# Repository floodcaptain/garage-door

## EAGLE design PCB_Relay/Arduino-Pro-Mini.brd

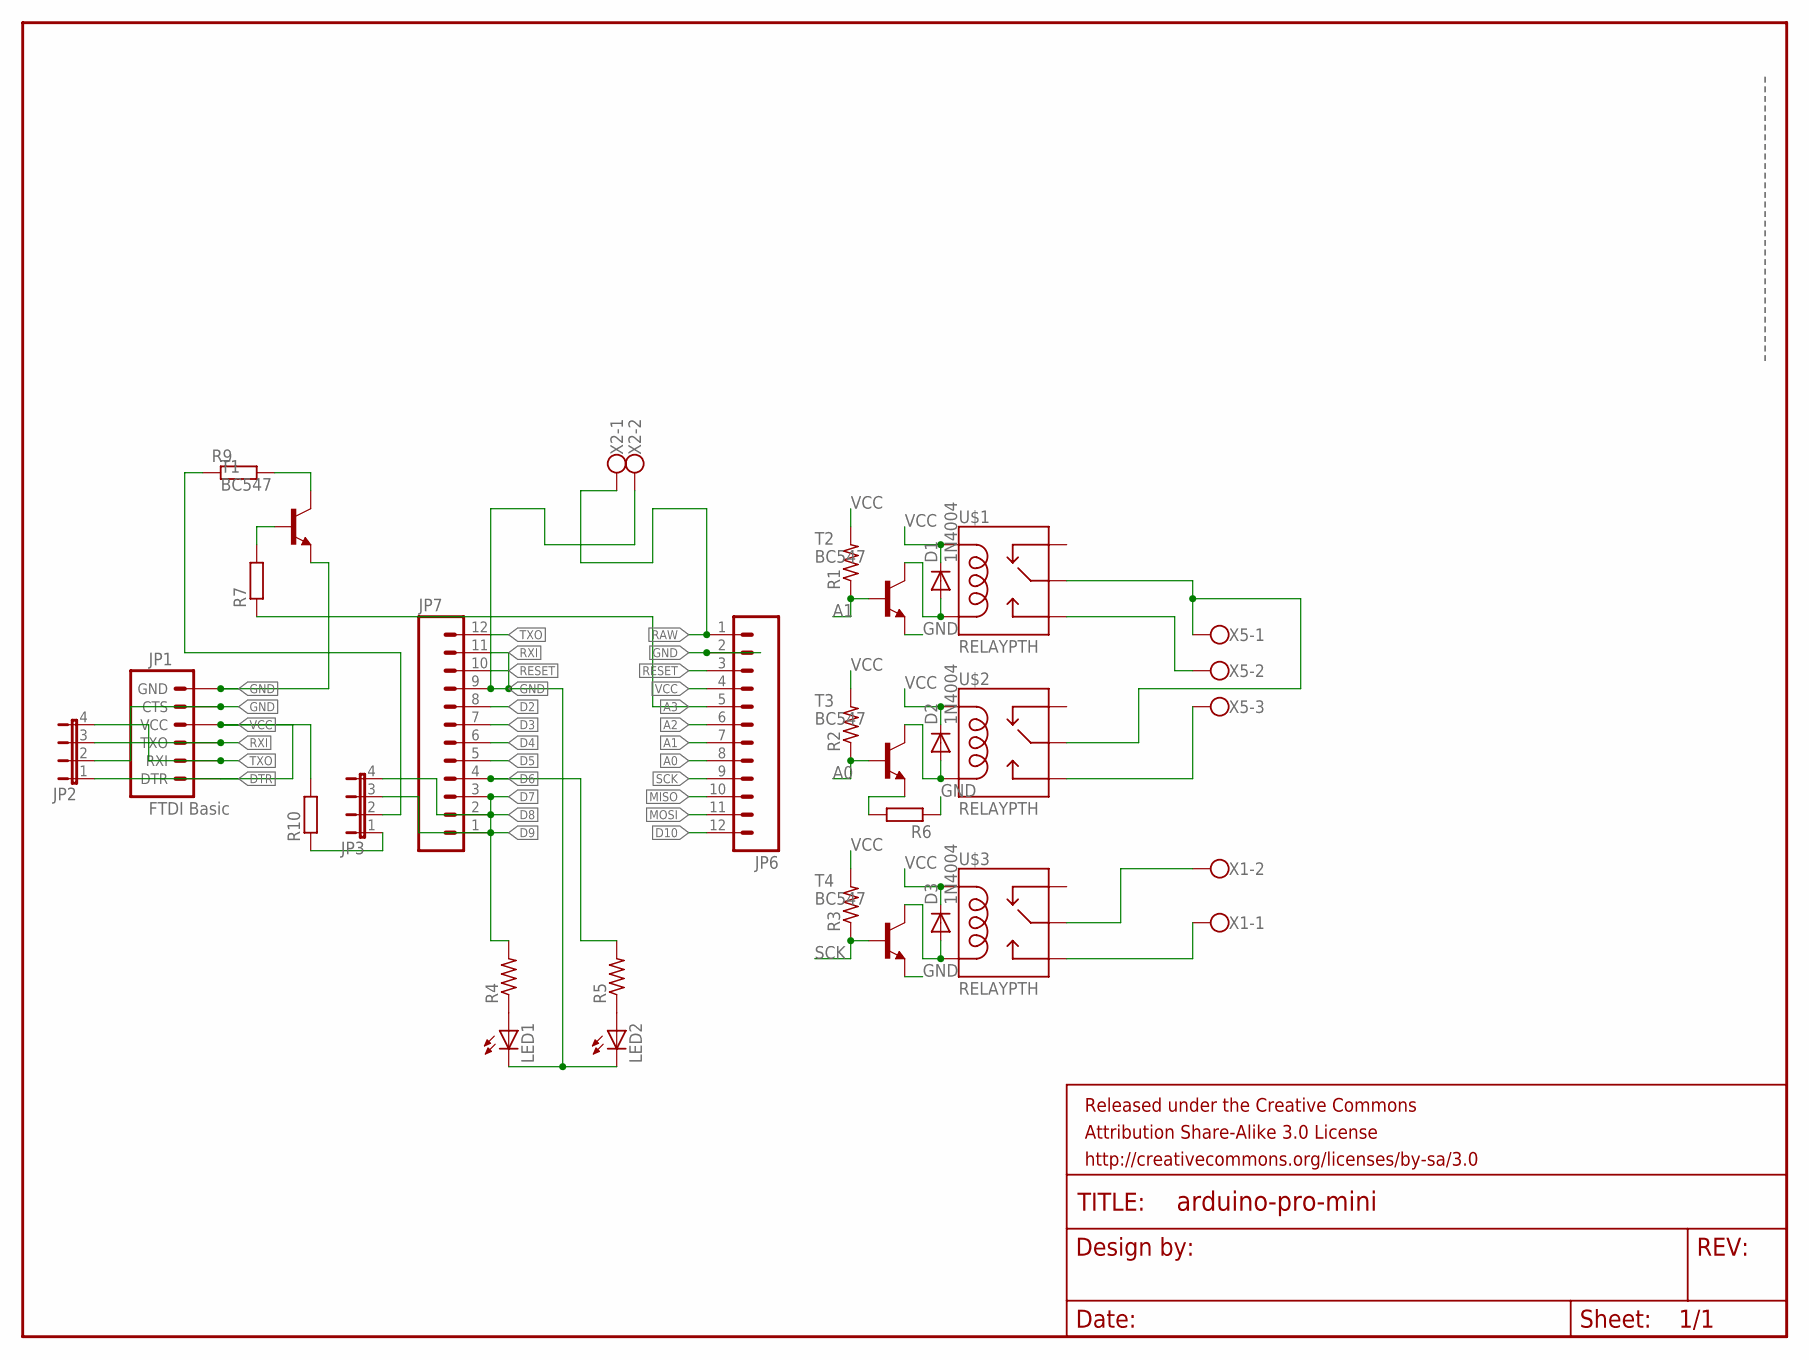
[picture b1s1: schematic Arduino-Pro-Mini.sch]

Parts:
D1, D2, D3: 1N4004; DO41-10
FRAME1: FRAME-LETTER; CREATIVE_COMMONS
JP1: FTDI Basic; 1X06
JP2, JP3: JP4E; JP4
JP6, JP7: M12PTH; 1X12
LED1, LED2: LED3MM
R1, R2, R3: R-US_0204/5; 0204/5
R4, R5: FLIPFLOP-RES; 0805-THM
R6, R10: RR1206; R1206
R7: R0204/7; 0204/7
R9: RR0603; R0603
T1, T2, T3, T4: BC547; TO92
U$1, U$2, U$3: RELAYPTH; SRD-05VDC-SL-C
X1, X2: W237-102
X5: W237-103

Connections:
A0: JP6.8, R2.1, T3.2 (B)
A1: JP6.7, R1.1, T2.2 (B)
A2: JP6.6
A3: JP6.5, R7.1
D2: JP7.8
D3: JP7.7
D4: JP7.6
D5: JP7.5
D6: JP7.4, R5.2
D7: JP7.3, R4.2
D8: JP3.4, JP7.2
D9: JP3.3, JP7.1
D10: JP6.12
DTR: JP1.1 (DTR)
GND: JP1.5 (CTS), JP1.6 (GND), JP2.2, JP6.2, JP7.9, LED1.K (C), LED2.K (C), R6.1, R6.2, T1.1 (E), T2.1 (E), T3.1 (E), T4.1 (E), X2.2
MISO: JP6.10
MOSI: JP6.11
unnamed: U$1.SWCOMMON, U$2.SWCOMMON, X5.1
unnamed: U$1.SWOPEN, X5.2
unnamed: U$2.SWOPEN, X5.3
unnamed: D3.A, T4.3 (C), U$3.COIL0
unnamed: D2.A, T3.3 (C), U$2.COIL0
unnamed: D1.A, T2.3 (C), U$1.COIL0
unnamed: U$3.SWCOMMON, X1.2
unnamed: U$3.SWOPEN, X1.1
unnamed: LED1.A, R4.1
unnamed: LED2.A, R5.1
unnamed: JP3.2, R9.1
unnamed: R7.2, T1.2 (B)
unnamed: JP3.1, R10.1
unnamed: R9.2, T1.3 (C)
RAW: JP6.1, X2.1
RESET: JP6.3, JP7.10
RXI: JP1.3 (TXO), JP2.3, JP7.11
SCK: JP6.9, R3.1, T4.2 (B)
TXO: JP1.2 (RXI), JP2.4, JP7.12
VCC: D1.C, D2.C, D3.C, JP1.4 (VCC), JP2.1, JP6.4, R1.2, R2.2, R3.2, R10.2, U$1.COIL1, U$2.COIL1, U$3.COIL1

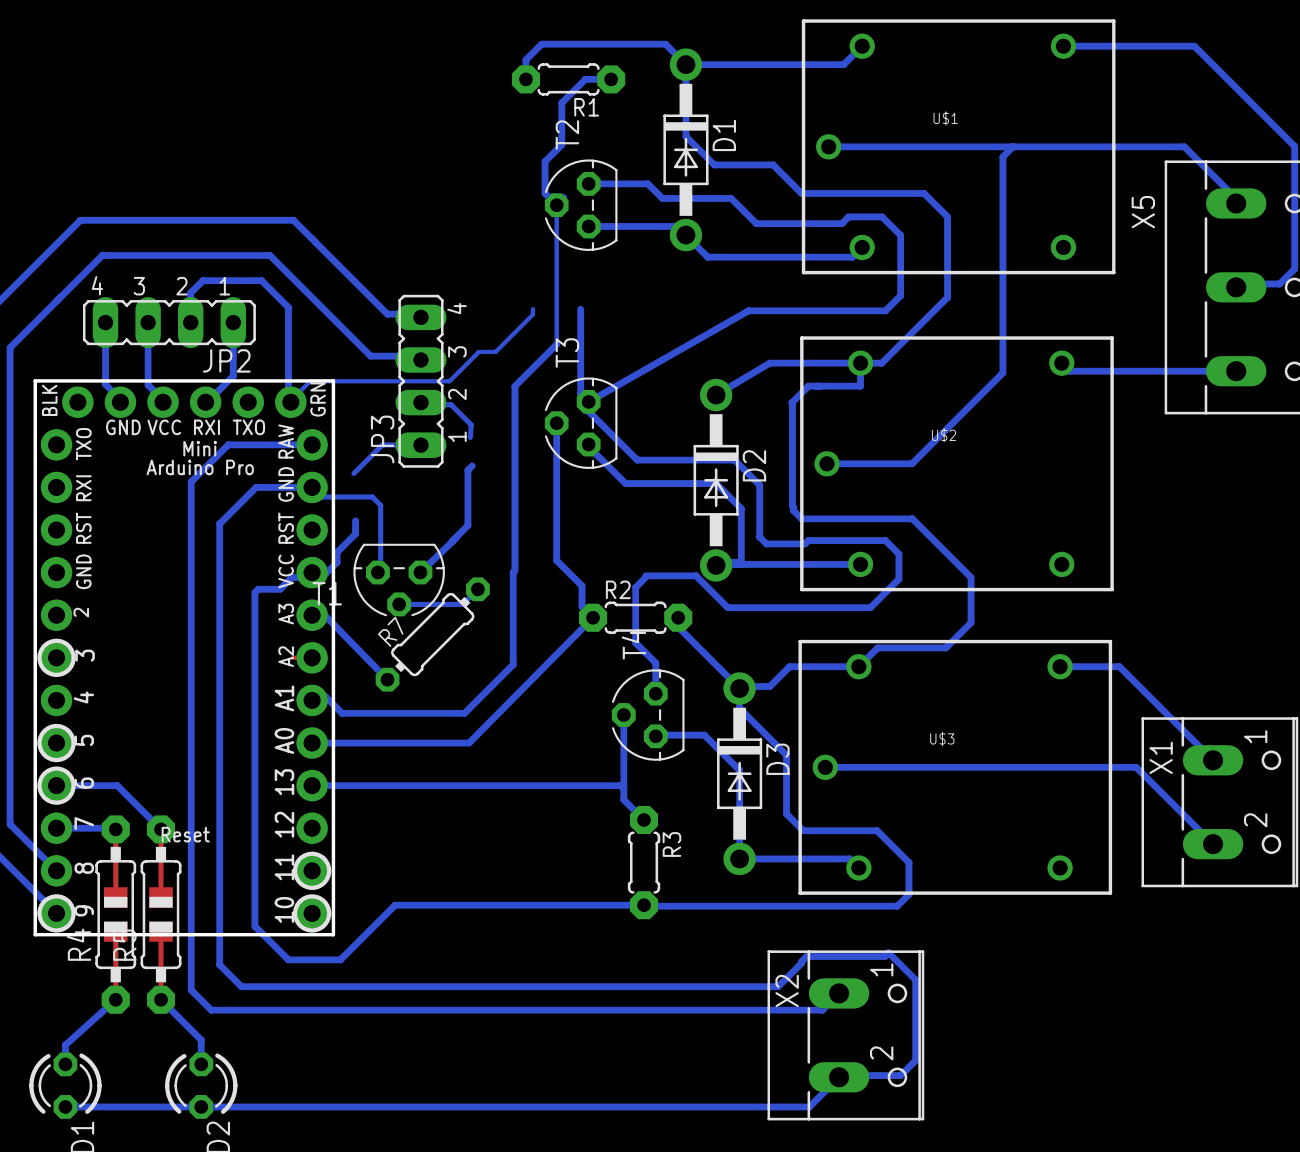
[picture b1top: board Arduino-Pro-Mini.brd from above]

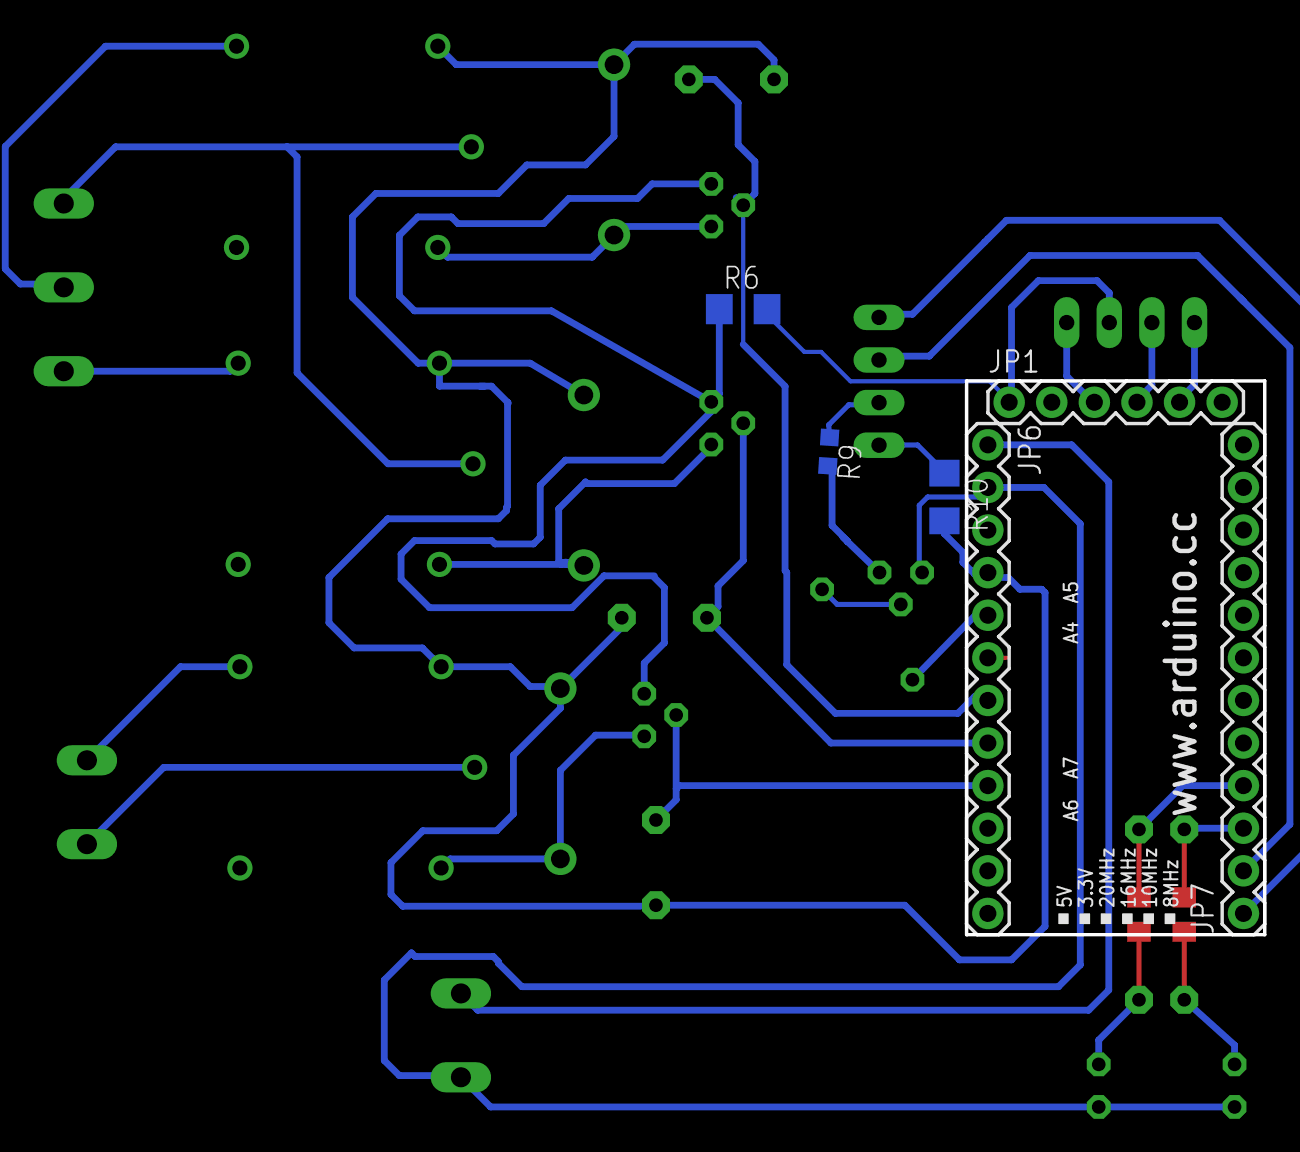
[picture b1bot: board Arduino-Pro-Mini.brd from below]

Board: 2 copper layers, 30 parts (6 on the bottom side), 28 nets.

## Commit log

2017-03-27 added eagle cad files
2017-04-07 pcb schematic and layout for relay added
2017-04-07 board file small change .
2017-04-10 added testing code
2017-06-01 code working good with ble

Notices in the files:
parts and their libraries:
SparkFun-Aesthetics: Licensing: CC v3.0 Share-Alike You are welcome to use this library for commercial purposes.
SparkFun-Aesthetics: Released under the Creative Commons Attribution Share-Alike 3.0 License
SparkFun-Aesthetics: http://creativecommons.org/licenses/by-sa/3.0
